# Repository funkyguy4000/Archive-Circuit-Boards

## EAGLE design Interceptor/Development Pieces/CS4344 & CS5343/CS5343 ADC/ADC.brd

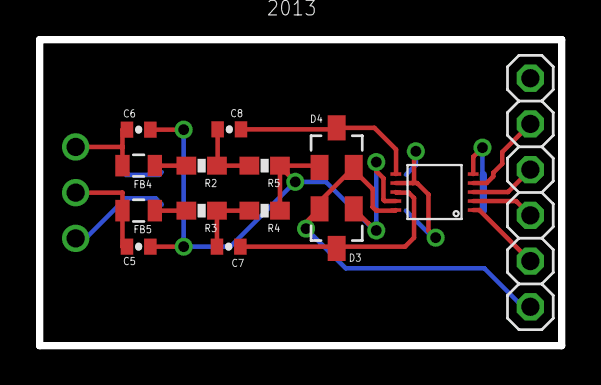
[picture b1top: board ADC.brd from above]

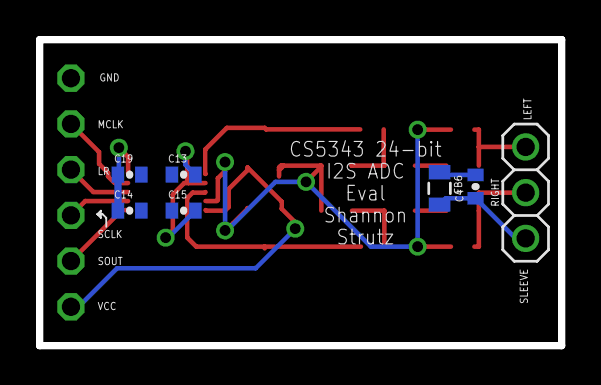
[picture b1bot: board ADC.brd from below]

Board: 2 copper layers, 29.0 x 17.0 mm, 21 parts (7 on the bottom side), 17 nets.

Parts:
C4, C5, C6: 1000pF; 0402-CAP
C7, C8, C15, C19: 1uF; 0402-CAP
C13, C14: .1uF; 0402-CAP
D3, D4: BAT54S; SOT23
FB4, FB5, FB6: 220; 0805
JP1: 1X06
JP3: 1X03
R2, R3: 6.81k; 0603-RES
R4, R5: 3.32k; 0603-RES
U$3: CS5343; TSSOP-10

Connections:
AINL: C6.1, FB4.2, JP3.1
AINL_C: C8.1, D4.3, U$3.6
AINL_FB: FB4.1, R2.2
AINL_R: C8.2, R2.1, R5.2
AINR: C5.1, FB5.2, JP3.2
AINR_C: C7.1, D3.3, U$3.8
AINR_FB: FB5.1, R3.2
AINR_R: C7.2, R3.1, R4.2
AIN_SLEEV: C4.1, FB6.2, JP3.3
GND: C4.2, C5.2, C6.2, C13.1, C14.2, C15.1, C19.2, D3.1, D4.1, FB6.1, JP1.1, R4.1, R5.1, U$3.9
LRCLK: JP1.3, U$3.3
MCLK: JP1.2, U$3.4
unnamed: C13.2, C15.2, U$3.7
unnamed: C14.1, C19.1, U$3.5
SCLK: JP1.4, U$3.2
SOUT: JP1.5, U$3.1
VCC: D3.2, D4.2, JP1.6, U$3.10

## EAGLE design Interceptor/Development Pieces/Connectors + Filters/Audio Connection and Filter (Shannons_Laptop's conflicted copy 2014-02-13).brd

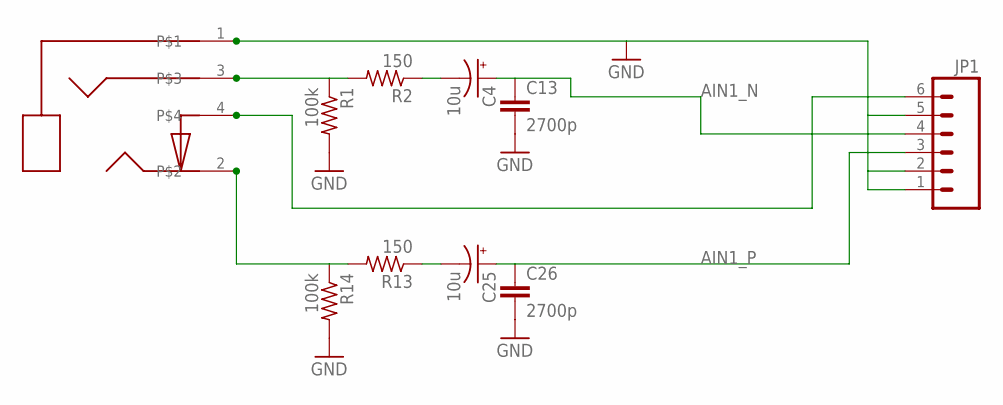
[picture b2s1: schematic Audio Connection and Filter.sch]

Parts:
C4, C25: 10u; PANASONIC_B
C13, C26: 2700p; 0402-CAP
J1: SJ1-3514-SMT
JP1: M06SMD; 1X06-SMD
R1, R14: 100k; R0402
R2, R13: 150; R0402

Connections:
AIN1_N: C4.+, C13.1, JP1.4
AIN1_P: C25.+, C26.1, JP1.3
CH1_IN: J1.4, JP1.6
GND: C13.2, C26.2, J1.1, JP1.1, JP1.2, JP1.5, R1.2, R14.2
unnamed: J1.2, R13.2, R14.1
unnamed: J1.3, R1.1, R2.2
unnamed: C4.-, R2.1
unnamed: C25.-, R13.1

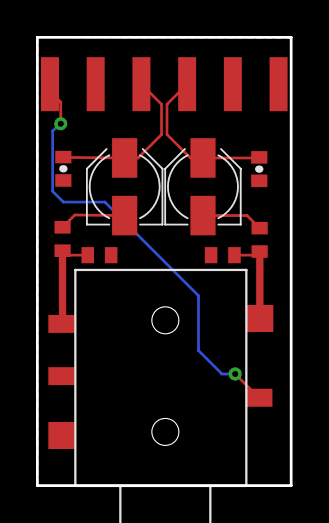
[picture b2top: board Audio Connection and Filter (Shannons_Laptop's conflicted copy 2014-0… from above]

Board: 2 copper layers, 14.1 x 24.9 mm, 10 parts (0 on the bottom side), 8 nets.

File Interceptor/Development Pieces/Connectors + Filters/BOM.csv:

"Part";"Value";"Device";"Package";"Description";"";
"C4";"10u";"CPOL-USB";"PANASONIC_B";"POLARIZED CAPACITOR, American symbol";"";
"C13";"2700p";"CAP0402-CAP";"0402-CAP";"Capacitor";"";
"C25";"10u";"CPOL-USB";"PANASONIC_B";"POLARIZED CAPACITOR, American symbol";"";
"C26";"2700p";"CAP0402-CAP";"0402-CAP";"Capacitor";"";
"J1";"SJ1-3514-SMT";"SJ1-3514-SMT";"SJ1-3514-SMT";"";"";
"JP1";"";"M06SMD";"1X06-SMD";"Header 6";"";
"R1";"100k";"R-US_R0402";"R0402";"RESISTOR, American symbol";"";
"R2";"150";"R-US_R0402";"R0402";"RESISTOR, American symbol";"";
"R13";"150";"R-US_R0402";"R0402";"RESISTOR, American symbol";"";
"R14";"100k";"R-US_R0402";"R0402";"RESISTOR, American symbol";"";

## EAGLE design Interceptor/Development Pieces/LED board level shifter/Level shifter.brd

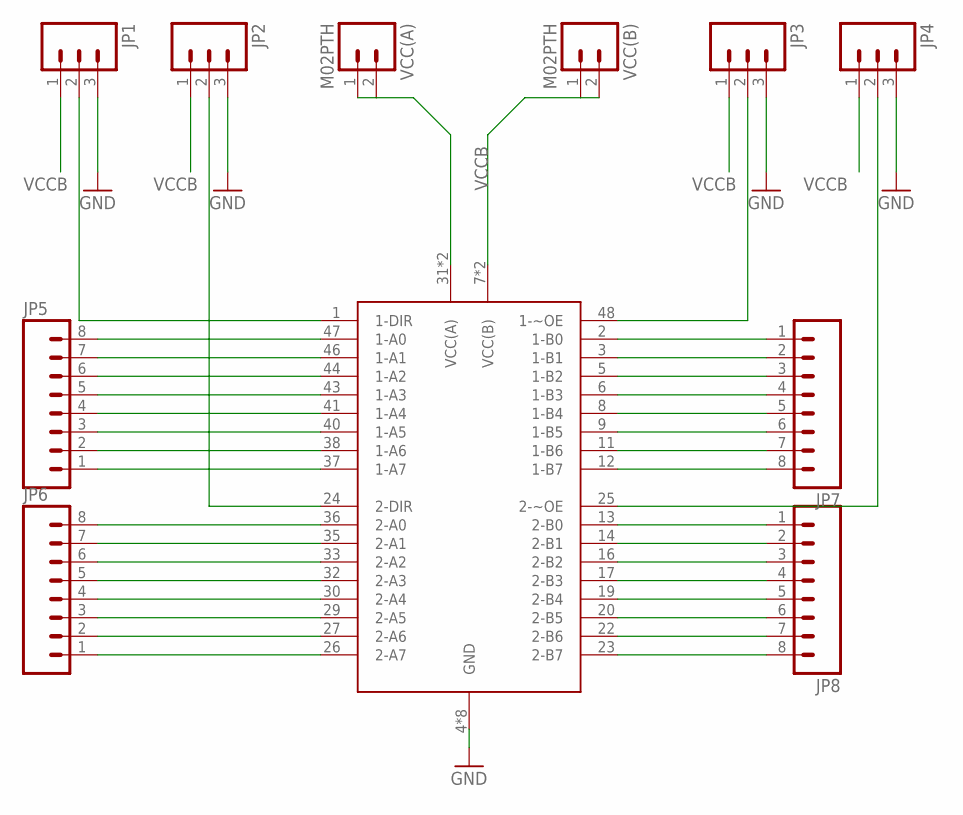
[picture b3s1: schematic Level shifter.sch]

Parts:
JP1, JP2, JP3, JP4: M03PTH; 1X03
JP5, JP6, JP7, JP8: M081X08; 1X08
U$1: 74AVC8T245TSSOP; TSSOP-48
VCC(A): M02PTH; 1X02
VCC(B): M02PTH; 1X02

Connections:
1-DIR: JP1.2, U$1.1 (1-DIR)
1-~OE: JP3.2, U$1.48 (1-~OE)
1A0: JP5.8, U$1.47 (1-A0)
1A1: JP5.7, U$1.46 (1-A1)
1A2: JP5.6, U$1.44 (1-A2)
1A3: JP5.5, U$1.43 (1-A3)
1A4: JP5.4, U$1.41 (1-A4)
1A5: JP5.3, U$1.40 (1-A5)
1A6: JP5.2, U$1.38 (1-A6)
1A7: JP5.1, U$1.37 (1-A7)
1B0: JP7.1, U$1.2 (1-B0)
1B1: JP7.2, U$1.3 (1-B1)
1B2: JP7.3, U$1.5 (1-B2)
1B3: JP7.4, U$1.6 (1-B3)
1B4: JP7.5, U$1.8 (1-B4)
1B5: JP7.6, U$1.9 (1-B5)
1B6: JP7.7, U$1.11 (1-B6)
1B7: JP7.8, U$1.12 (1-B7)
2-DIR: JP2.2, U$1.24 (2-DIR)
2-~OE: JP4.2, U$1.25 (2-~OE)
2A0: JP6.8, U$1.36 (2-A0)
2A1: JP6.7, U$1.35 (2-A1)
2A2: JP6.6, U$1.33 (2-A2)
2A3: JP6.5, U$1.32 (2-A3)
2A4: JP6.4, U$1.30 (2-A4)
2A5: JP6.3, U$1.29 (2-A5)
2A6: JP6.2, U$1.27 (2-A6)
2A7: JP6.1, U$1.26 (2-A7)
2B0: JP8.1, U$1.13 (2-B0)
2B1: JP8.2, U$1.14 (2-B1)
2B2: JP8.3, U$1.16 (2-B2)
2B3: JP8.4, U$1.17 (2-B3)
2B4: JP8.5, U$1.19 (2-B4)
2B5: JP8.6, U$1.20 (2-B5)
2B6: JP8.7, U$1.22 (2-B6)
2B7: JP8.8, U$1.23 (2-B7)
GND: JP1.3, JP2.3, JP3.3, JP4.3, U$1.4 (GND), U$1.10 (GND), U$1.15 (GND), U$1.21 (GND), U$1.28 (GND), U$1.34 (GND), U$1.39 (GND), U$1.45 (GND)
VCC(A): U$1.31 (VCC(A)), U$1.42 (VCC(A)), VCC(A).1, VCC(A).2
VCCB: JP1.1, JP2.1, JP3.1, JP4.1, U$1.7 (VCC(B)), U$1.18 (VCC(B)), VCC(B).1, VCC(B).2

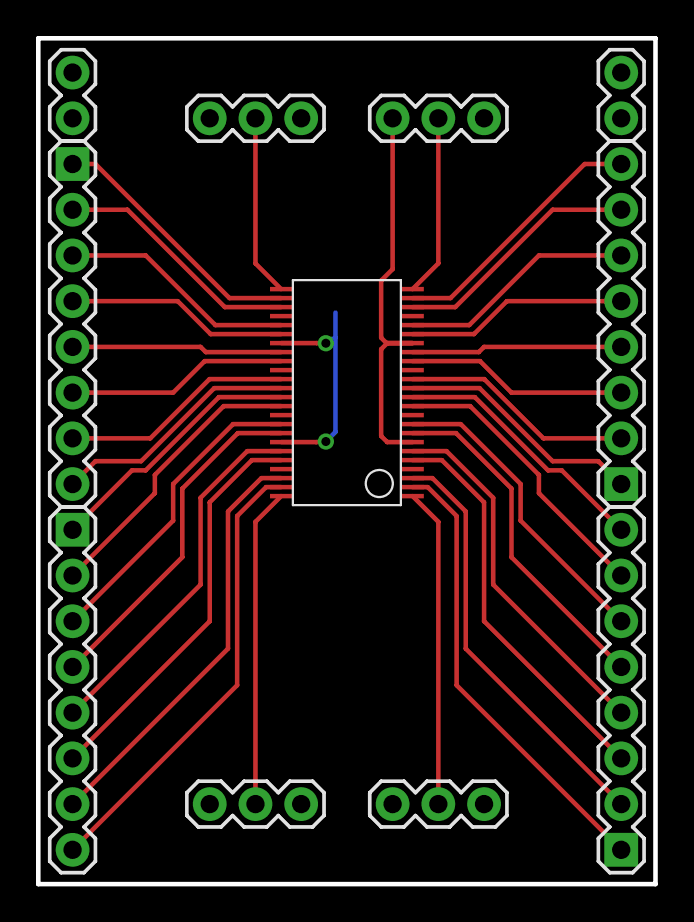
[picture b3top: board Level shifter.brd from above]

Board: 2 copper layers, 34.3 x 47.0 mm, 11 parts (0 on the bottom side), 39 nets.

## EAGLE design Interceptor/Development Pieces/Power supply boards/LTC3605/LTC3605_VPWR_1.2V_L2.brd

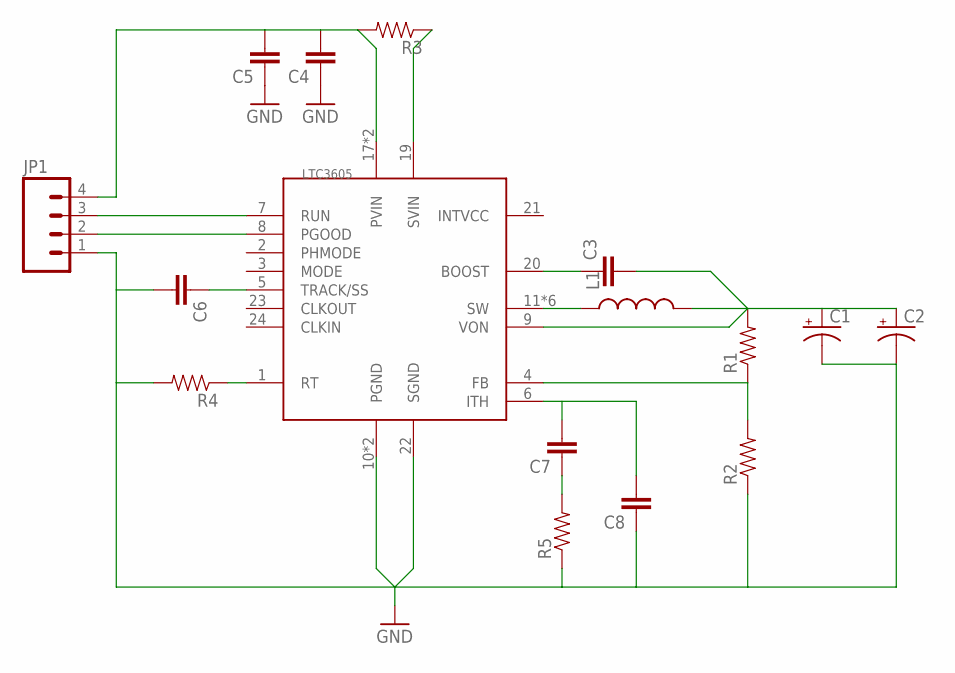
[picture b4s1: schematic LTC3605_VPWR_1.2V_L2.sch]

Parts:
C1, C2: CAP_POL1206; EIA3216
C3, C4, C5, C6, C7, C8: CAP0603-CAP; 0603-CAP
JP1: M04LOCK; 1X04_LOCK
L1: INDUCTORCR75; CR75
R1, R2, R3, R4, R5: RESISTOR0603-RES; 0603-RES
U$1: LTC3605; QFN24

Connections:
GND: C1.C (-), C2.C (-), C4.1, C5.1, C6.2, C8.1, JP1.1, R2.1, R4.2, R5.1, U$1.10 (PGND), U$1.22 (SGND), U$1.EXP (PGND)
ITH: C7.2, C8.2, U$1.6 (ITH)
unnamed: R1.1, R2.2, U$1.4 (FB)
unnamed: C1.A (+), C2.A (+), C3.2, L1.P$2 (2), R1.2, U$1.9 (VON)
unnamed: C3.1, U$1.20 (BOOST)
unnamed: R3.1, U$1.19 (SVIN)
unnamed: C7.1, R5.2
unnamed: JP1.2, U$1.8 (PGOOD)
unnamed: JP1.3, U$1.7 (RUN)
unnamed: C4.2, C5.2, JP1.4, R3.2, U$1.17 (PVIN), U$1.18 (PVIN)
RT: R4.1, U$1.1 (RT)
SW: L1.P$1 (1), U$1.11 (SW), U$1.12 (SW), U$1.13 (SW), U$1.14 (SW), U$1.15 (SW), U$1.16 (SW)
TRACK/SS: C6.1, U$1.5 (TRACK/SS)

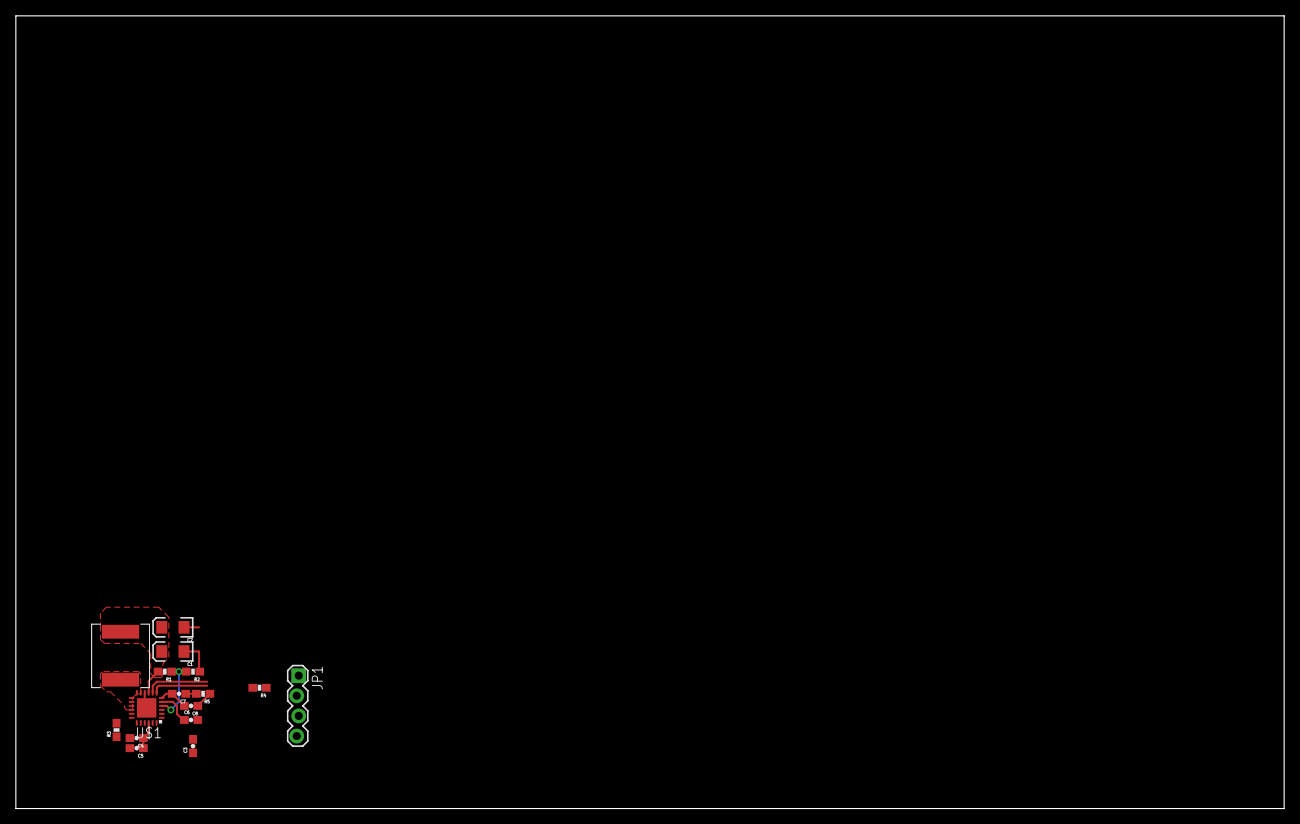
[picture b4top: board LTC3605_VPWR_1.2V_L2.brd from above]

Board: 2 copper layers, 160.0 x 100.0 mm, 16 parts (0 on the bottom side), 13 nets.

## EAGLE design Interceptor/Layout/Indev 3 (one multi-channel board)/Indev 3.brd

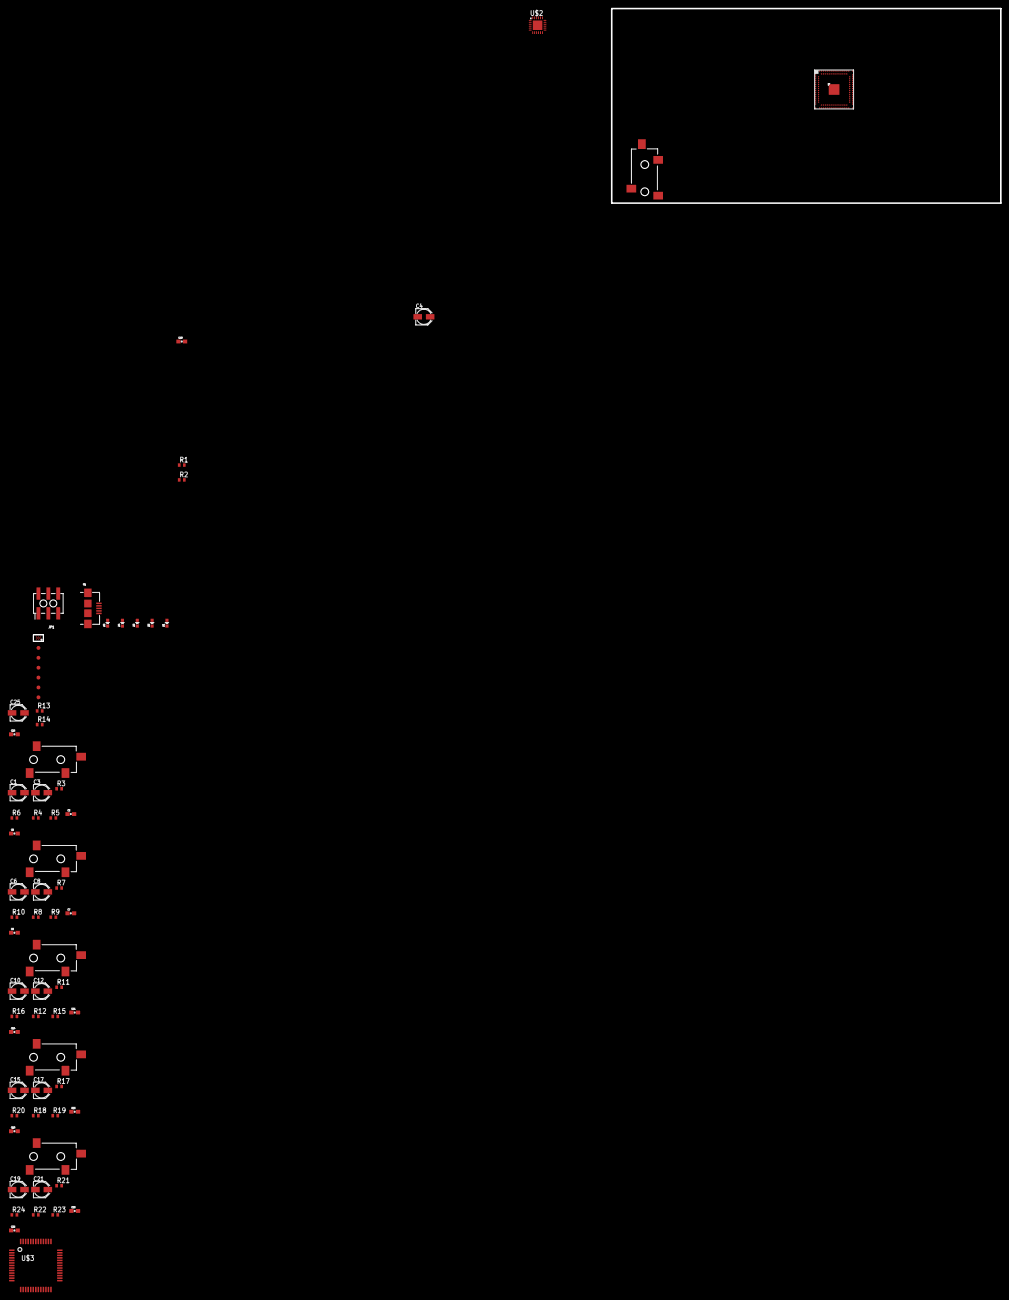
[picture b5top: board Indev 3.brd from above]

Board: 2 copper layers, 71 parts (0 on the bottom side), 37 nets, no tracks yet.

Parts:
C1, C3, C4, C6, C8, C10, C12, C15, C17, C19, C21, C25: 10u; PANASONIC_B
C2, C5, C7, C9, C11, C13, C14, C16, C18, C20, C22, C26: 2700p; 0603-CAP
D1, D2, D3, D4, D5: GREEN; LED-0603
J1, J2, J3, J4, J5, J6: SJ3524_AUDIO
JP1: 2X3_SMT_POSTS
JP2, JP3, JP4, JP5, JP6, JP7: FIDUCIAL1X2; FIDUCIAL-1X2
R1, R3, R6, R7, R10, R11, R14, R16, R17, R20, R21, R24: 100k; R0402
R2, R4, R5, R8, R9, R12, R13, R15, R18, R19, R22, R23: 150; R0402
U1: USB-AB-MICRO-SMD
U$1: XS1-L8A-128-QF124; QFN-124
U$2: LTC3605; QFN24
U$3: CS42436; QFP-52
U$6: M24M01

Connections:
AIN1+: C25.+, C26.1, U$3.39
AIN1-: C4.+, C13.1, U$3.38
AIN2+: C3.+, C5.1, U$3.41
AIN2-: C1.+, C2.1, U$3.40
AIN3+: C8.+, C9.1, U$3.43
AIN3-: C6.+, C7.1, U$3.42
GND: C2.2, C5.2, C7.2, C9.2, C11.2, C13.2, C14.2, C16.2, C18.2, C20.2, C22.2, C26.2, J1.SLEEVE, J2.SLEEVE, J3.SLEEVE, J4.SLEEVE, J5.SLEEVE, J6.SLEEVE, R1.2, R3.2, R6.2, R7.2, R10.2, R11.2, R14.2, R16.2, R17.2, R20.2, R21.2, R24.2, U$3.3, U$3.4
unnamed: J1.TIP, R13.2, R14.1
unnamed: J1.RING, R1.1, R2.2
unnamed: C4.-, R2.1
unnamed: C25.-, R13.1
unnamed: J2.RING, R3.1, R4.2
unnamed: C1.-, R4.1
unnamed: J2.TIP, R5.2, R6.1
unnamed: C3.-, R5.1
unnamed: J3.RING, R7.1, R8.2
unnamed: C6.-, R8.1
unnamed: J3.TIP, R9.2, R10.1
unnamed: C8.-, R9.1
unnamed: J4.RING, R11.1, R12.2
unnamed: C10.-, R12.1
unnamed: C10.+, C11.1
unnamed: J4.TIP, R15.2, R16.1
unnamed: C12.-, R15.1
unnamed: C12.+, C14.1
unnamed: J5.RING, R17.1, R18.2
unnamed: C15.-, R18.1
unnamed: C15.+, C16.1
unnamed: J5.TIP, R19.2, R20.1
unnamed: C17.-, R19.1
unnamed: C17.+, C18.1
unnamed: J6.RING, R21.1, R22.2
unnamed: C19.-, R22.1
unnamed: C19.+, C20.1
unnamed: J6.TIP, R23.2, R24.1
unnamed: C21.-, R23.1
unnamed: C21.+, C22.1

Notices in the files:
Interceptor/Development Pieces/CS4344 & CS5343/CS5343 ADC/ADC.brd:
License CC BY-NC-SA 3.0
parts and their libraries:
SparkFun-Passives: Licensing: CC v3.0 Share-Alike You are welcome to use this library for commercial purposes.
